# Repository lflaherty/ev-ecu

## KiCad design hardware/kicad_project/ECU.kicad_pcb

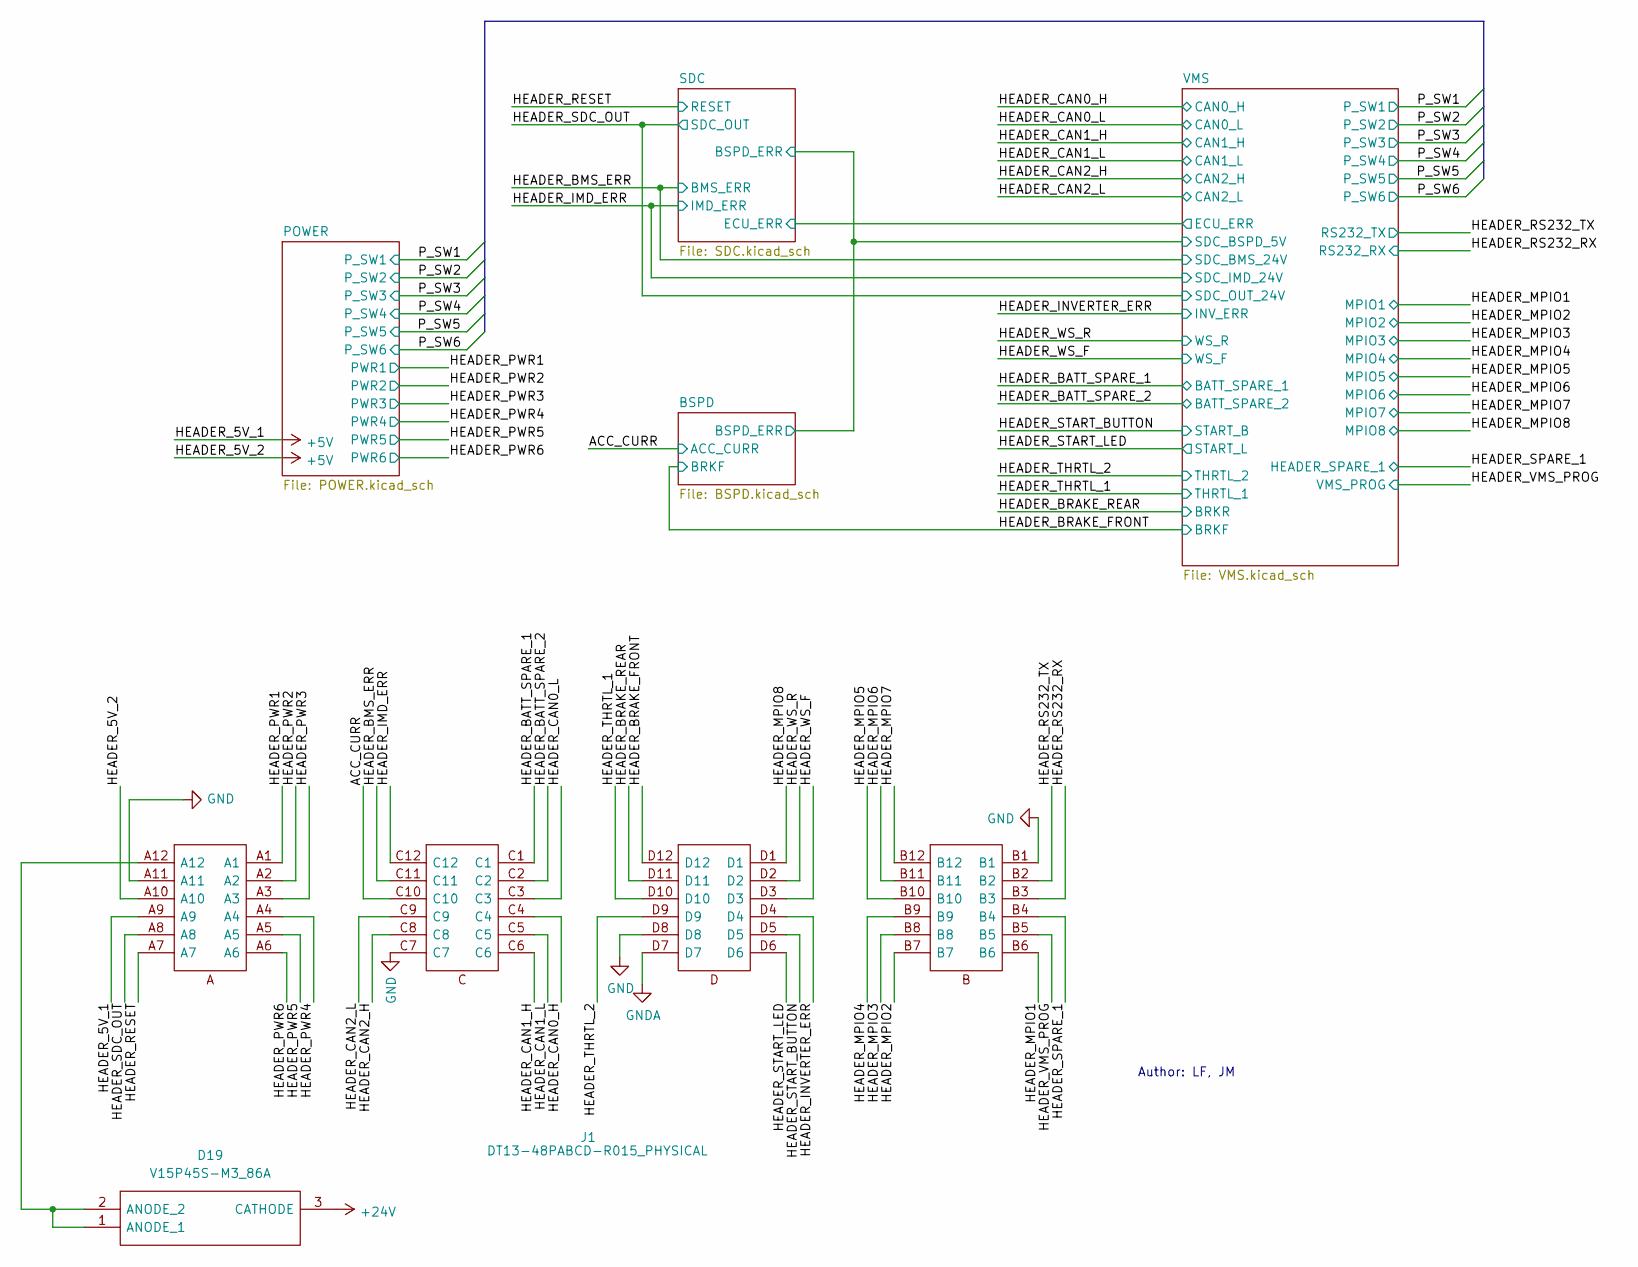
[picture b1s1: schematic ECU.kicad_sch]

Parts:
D19: V15P45S-M3_86A; V15P45SM387A; Manufacturer_Part_Number V15P45S-M3/87A; Mouser Part Number 78-V15P45S-M387A
J1: DT13-48PABCD-R015_PHYSICAL; DT1348PABCDR015_PHYSICAL; Manufacturer_Part_Number DT13-48PABCD-R015; Mouser Part Number 571-DT13-48PABCDR015

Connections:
+5V: J1.A9, J1.A10; also elsewhere on the board
+24V: D19.3 (CATHODE); also elsewhere on the board
/BSPD/ACC_CURR: J1.C10; also elsewhere on the board
/BSPD/BRKF: J1.D12; also elsewhere on the board
/POWER/PWR1: J1.A1; also elsewhere on the board
/POWER/PWR2: J1.A2; also elsewhere on the board
/POWER/PWR3: J1.A3; also elsewhere on the board
/POWER/PWR4: J1.A4; also elsewhere on the board
/POWER/PWR5: J1.A5; also elsewhere on the board
/POWER/PWR6: J1.A6; also elsewhere on the board
/SDC/BMS_ERR: J1.C11; also elsewhere on the board
/SDC/IMD_ERR: J1.C12; also elsewhere on the board
/SDC/RESET: J1.A7; also elsewhere on the board
/SDC/SDC_OUT: J1.A8; also elsewhere on the board
/VMS/BATT_SPARE_1: J1.C1; also elsewhere on the board
/VMS/BATT_SPARE_2: J1.C2; also elsewhere on the board
/VMS/BRKR: J1.D11; also elsewhere on the board
/VMS/CAN0_H: J1.C3; also elsewhere on the board
/VMS/CAN0_L: J1.C4; also elsewhere on the board
/VMS/CAN1_H: J1.C5; also elsewhere on the board
/VMS/CAN1_L: J1.C6; also elsewhere on the board
/VMS/CAN2_H: J1.C9; also elsewhere on the board
/VMS/CAN2_L: J1.C8; also elsewhere on the board
/VMS/HEADER_SPARE_1: J1.B4; also elsewhere on the board
/VMS/INV_ERR: J1.D4; also elsewhere on the board
/VMS/MPIO/MPIO1: J1.B6; also elsewhere on the board
/VMS/MPIO/MPIO2: J1.B7; also elsewhere on the board
/VMS/MPIO/MPIO3: J1.B8; also elsewhere on the board
/VMS/MPIO/MPIO4: J1.B9; also elsewhere on the board
/VMS/MPIO/MPIO5: J1.B10; also elsewhere on the board
/VMS/MPIO/MPIO6: J1.B11; also elsewhere on the board
/VMS/MPIO/MPIO7: J1.B12; also elsewhere on the board
/VMS/MPIO/MPIO8: J1.D1; also elsewhere on the board
/VMS/RS232_RX: J1.B3; also elsewhere on the board
/VMS/RS232_TX: J1.B2; also elsewhere on the board
/VMS/START_B: J1.D5; also elsewhere on the board
/VMS/START_L: J1.D6; also elsewhere on the board
/VMS/THRTL_1: J1.D10; also elsewhere on the board
/VMS/THRTL_2: J1.D9; also elsewhere on the board
/VMS/VMS_PROG: J1.B5; also elsewhere on the board
/VMS/WS_F: J1.D3; also elsewhere on the board
/VMS/WS_R: J1.D2; also elsewhere on the board
GND: J1.A11, J1.B1, J1.C7, J1.D8; also elsewhere on the board
GNDA: J1.D7
unnamed: D19.1 (ANODE_1), D19.2 (ANODE_2), J1.A12

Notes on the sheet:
Author: LF, JM

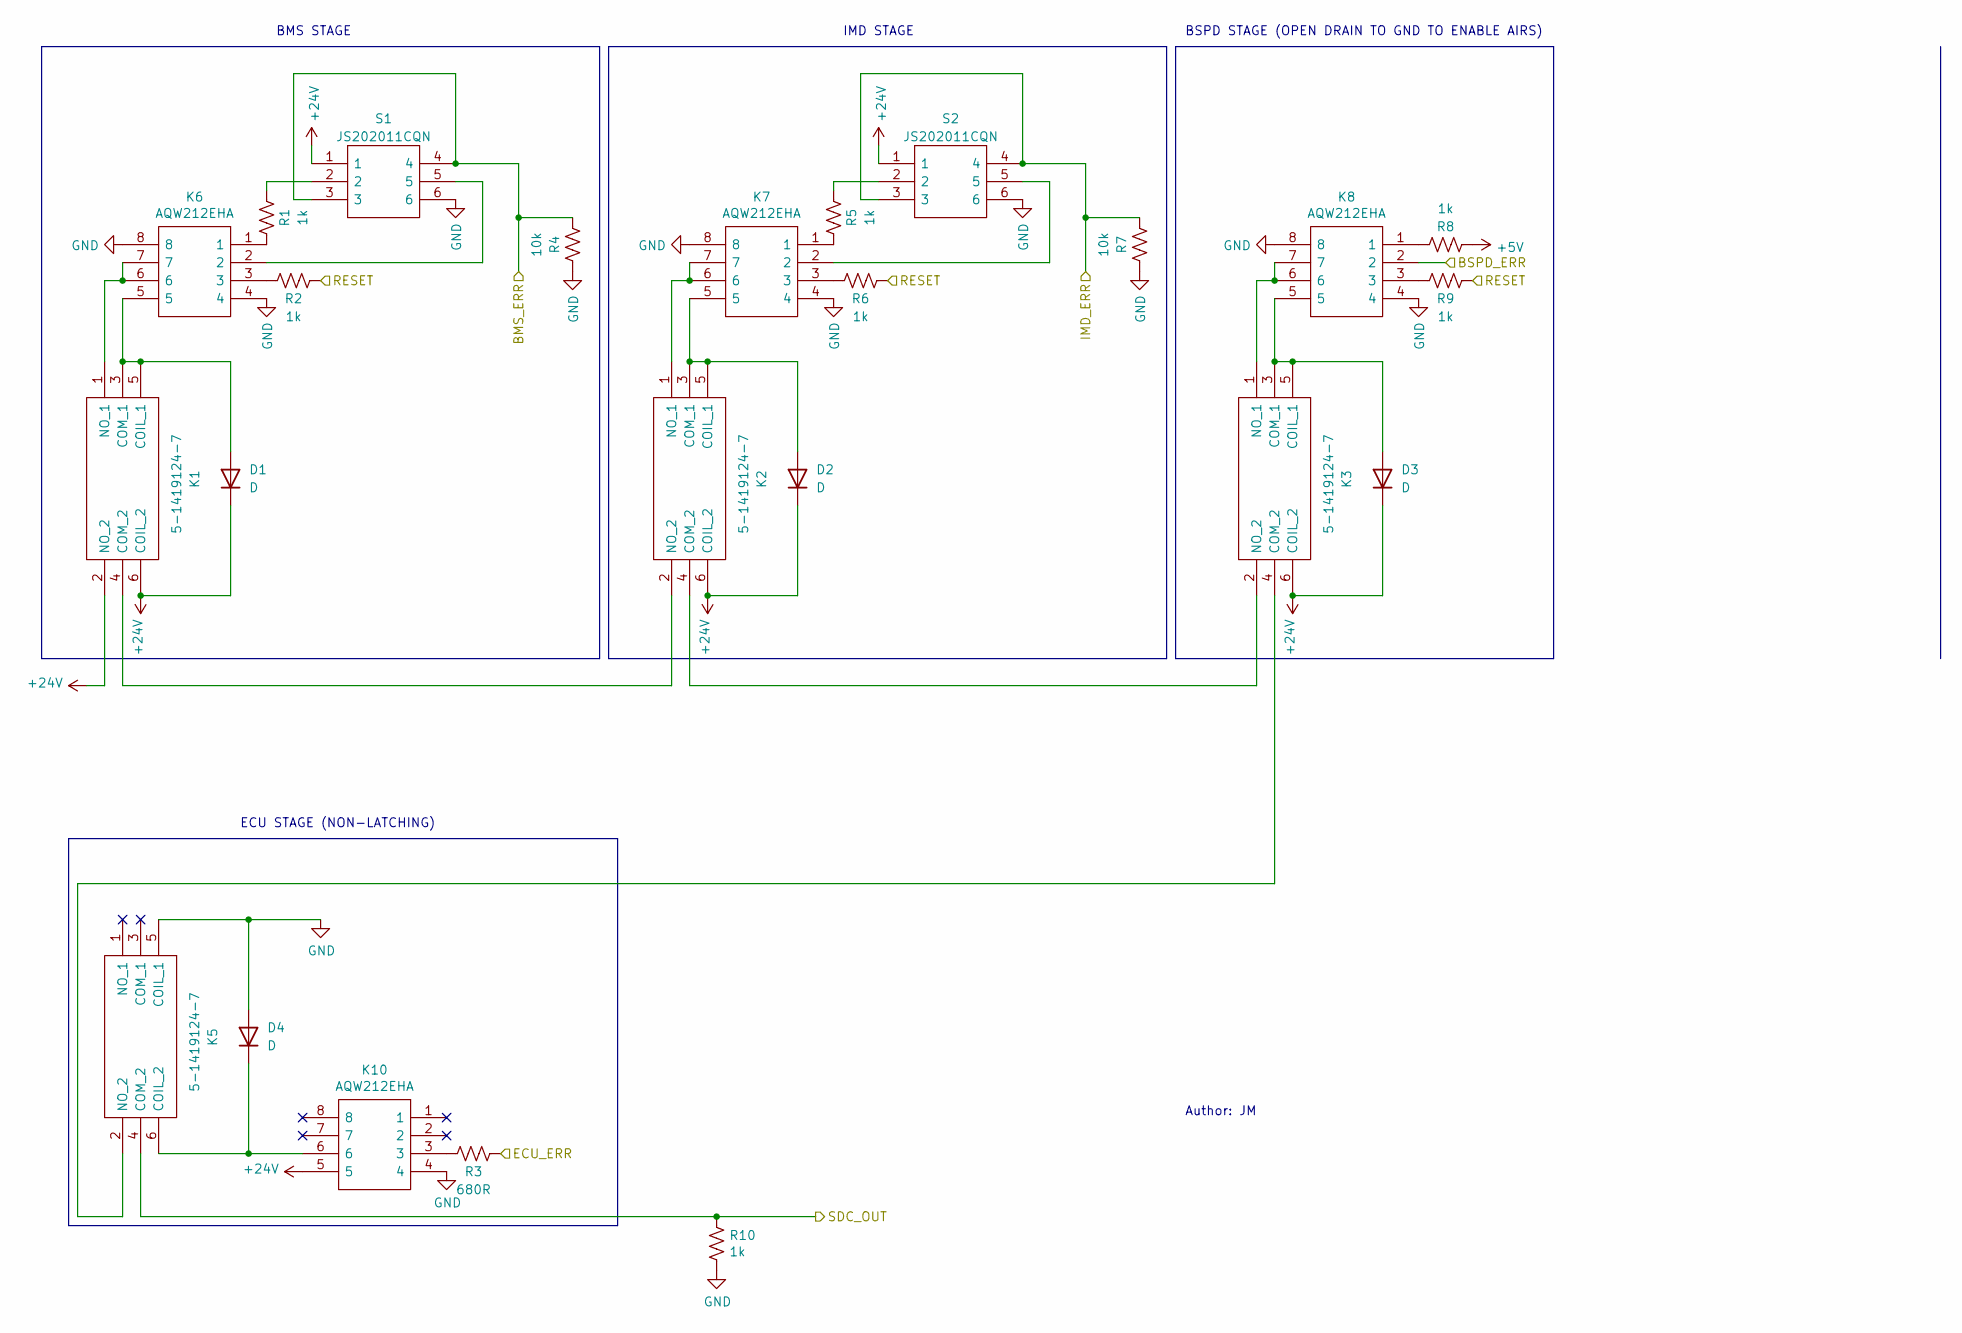
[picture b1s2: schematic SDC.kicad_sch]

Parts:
D1, D2, D3, D4: D; D_SMA
K1, K2, K3, K5: 5-1419124-7; 514191247; Manufacturer_Part_Number 5-1419124-7; Mouser Part Number 655-5-1419124-7
K6, K7, K8, K10: AQW212EHA; SOP254P962X275-8N; Manufacturer_Part_Number AQW212EHA; Mouser Part Number 769-AQW212EHA
R1, R2, R5, R6, R8, R9, R10: 1k; R_0805_2012Metric
R3: 680R; R_0805_2012Metric
R4, R7: 10k; R_0805_2012Metric
S1, S2: JS202011CQN; Manufacturer_Part_Number JS202011CQN; Mouser Part Number 611-JS202011CQN

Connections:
+5V: R8.2; also elsewhere on the board
+24V: D1.1 (K), D2.1 (K), D3.1 (K), K1.2 (NO_2), K1.6 (COIL_2), K2.6 (COIL_2), K3.6 (COIL_2), K10.5, S1.1, S2.1; also elsewhere on the board
/BSPD/BSPD_ERR: K8.2; also elsewhere on the board
/SDC/BMS_ERR: R4.2, S1.3, S1.4; also elsewhere on the board
/SDC/ECU_ERR: R3.1; also elsewhere on the board
/SDC/IMD_ERR: R7.2, S2.3, S2.4; also elsewhere on the board
/SDC/RESET: R2.1, R6.1, R9.1; also elsewhere on the board
/SDC/SDC_OUT: K5.4 (COM_2), R10.1; also elsewhere on the board
GND: D4.2 (A), K5.5 (COIL_1), K6.4, K6.8, K7.4, K7.8, K8.4, K8.8, K10.4, R4.1, R7.1, R10.2, S1.6, S2.6; also elsewhere on the board
unnamed: D1.2 (A), K1.3 (COM_1), K1.5 (COIL_1), K6.5
unnamed: D2.2 (A), K2.3 (COM_1), K2.5 (COIL_1), K7.5
unnamed: D3.2 (A), K3.3 (COM_1), K3.5 (COIL_1), K8.5
unnamed: D4.1 (K), K5.6 (COIL_2), K10.6
unnamed: K1.1 (NO_1), K6.6, K6.7
unnamed: K1.4 (COM_2), K2.2 (NO_2)
unnamed: K2.1 (NO_1), K7.6, K7.7
unnamed: K2.4 (COM_2), K3.2 (NO_2)
unnamed: K3.1 (NO_1), K8.6, K8.7
unnamed: K3.4 (COM_2), K5.2 (NO_2)
unnamed: K6.1, R1.2
unnamed: K6.2, S1.5
unnamed: K6.3, R2.2
unnamed: K7.1, R5.2
unnamed: K7.2, S2.5
unnamed: K7.3, R6.2
unnamed: K8.1, R8.1
unnamed: K8.3, R9.2
unnamed: K10.3, R3.2
unnamed: R1.1, S1.2
unnamed: R5.1, S2.2

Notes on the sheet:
ECU STAGE (NON-LATCHING)
BMS STAGE
Author: JM
BSPD STAGE (OPEN DRAIN TO GND TO ENABLE AIRS)
IMD STAGE

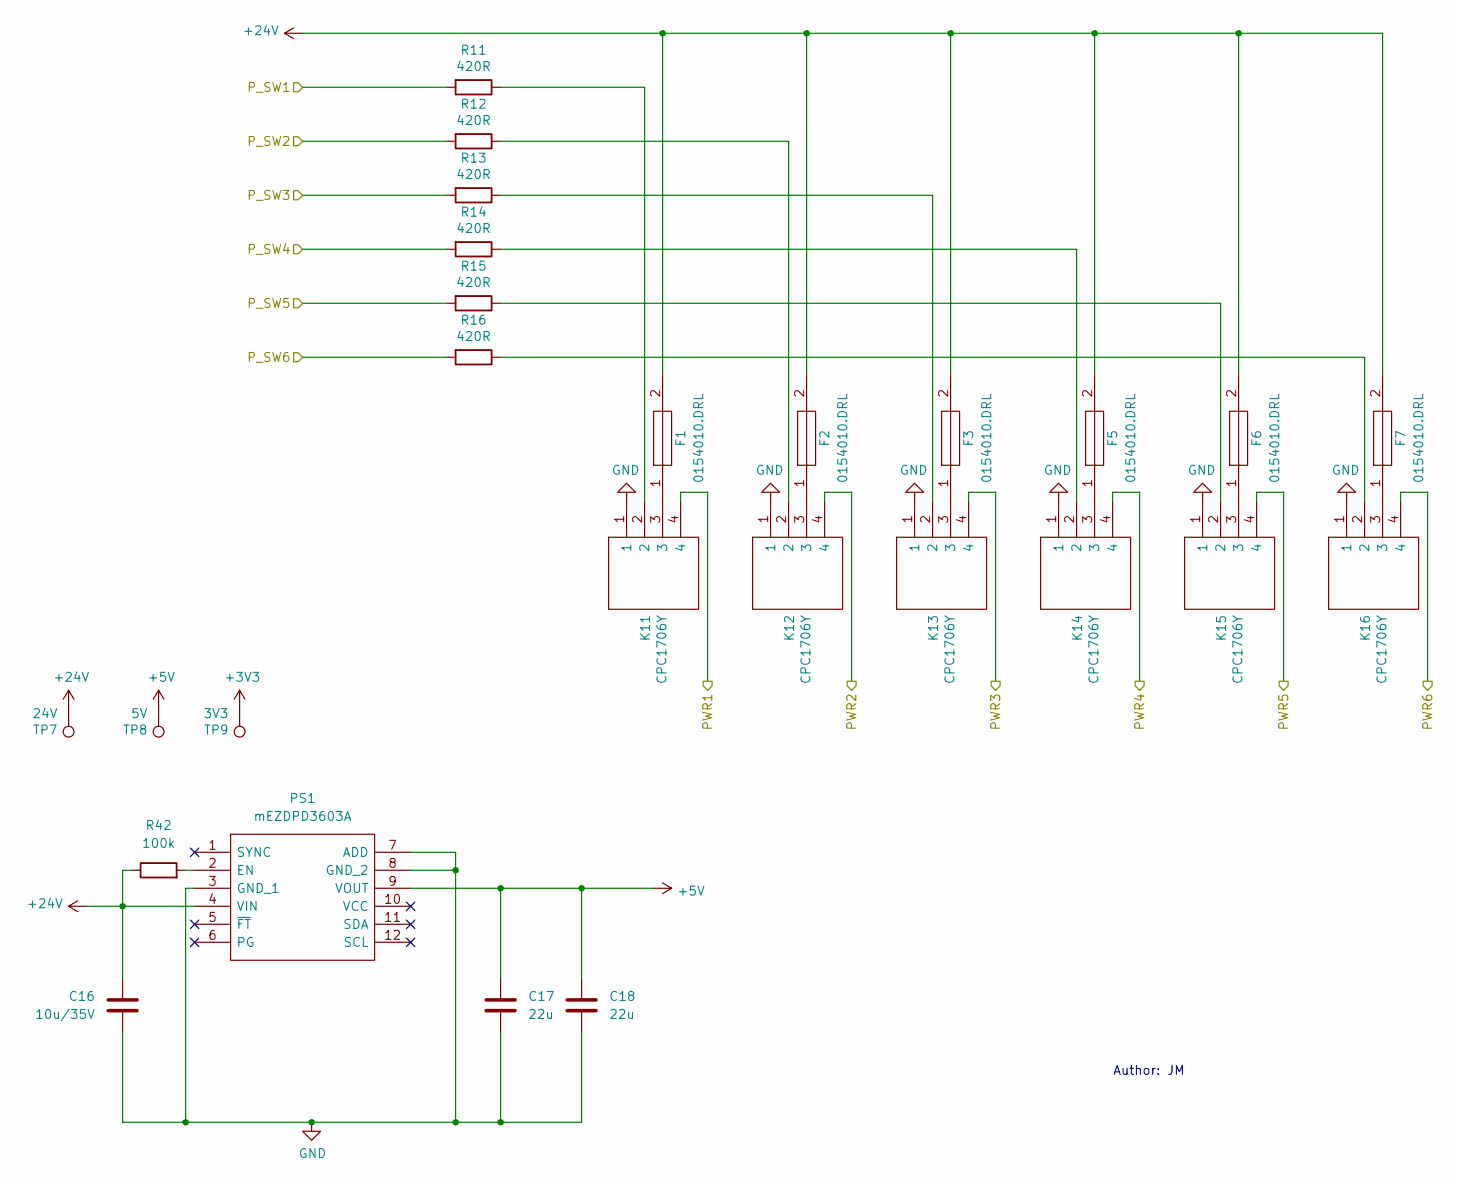
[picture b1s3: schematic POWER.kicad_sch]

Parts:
C16: 10u/35V; C_0805_2012Metric
C17, C18: 22u; C_1206_3216Metric
F1, F2, F3, F5, F6, F7: 0154010.DRL; 0154010DRL; Manufacturer_Part_Number 0154010.DRL; Mouser Part Number 576-0154010.DRL
K11, K12, K13, K14, K15, K16: CPC1706Y; Manufacturer_Part_Number CPC1706Y; Mouser Part Number 849-CPC1706Y
PS1: mEZDPD3603A; Manufacturer_Part_Number mEZDPD3603A; Mouser Part Number 946-MEZDPD3603A
R11, R12, R13, R14, R15, R16: 420R; R_0805_2012Metric
R42: 100k; R_0805_2012Metric
TP7: 24V; TestPoint_THTPad_D2.5mm_Drill1.2mm
TP8: 5V; TestPoint_THTPad_D2.5mm_Drill1.2mm
TP9: 3V3; TestPoint_THTPad_D2.5mm_Drill1.2mm

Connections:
+5V: C17.1, C18.1, PS1.9 (VOUT), TP8.1; also elsewhere on the board
+24V: C16.2, F1.2, F2.2, F3.2, F5.2, F6.2, F7.2, PS1.4 (VIN), R42.1, TP7.1; also elsewhere on the board
/POWER/PWR1: K11.4; also elsewhere on the board
/POWER/PWR2: K12.4; also elsewhere on the board
/POWER/PWR3: K13.4; also elsewhere on the board
/POWER/PWR4: K14.4; also elsewhere on the board
/POWER/PWR5: K15.4; also elsewhere on the board
/POWER/PWR6: K16.4; also elsewhere on the board
/POWER/P_SW1: R11.2; also elsewhere on the board
/POWER/P_SW2: R12.2; also elsewhere on the board
/POWER/P_SW3: R13.2; also elsewhere on the board
/POWER/P_SW4: R14.2; also elsewhere on the board
/POWER/P_SW5: R15.2; also elsewhere on the board
/POWER/P_SW6: R16.2; also elsewhere on the board
GND: C16.1, C17.2, C18.2, K11.1, K12.1, K13.1, K14.1, K15.1, K16.1, PS1.3 (GND_1), PS1.7 (ADD), PS1.8 (GND_2); also elsewhere on the board
unnamed: F1.1, K11.3
unnamed: F2.1, K12.3
unnamed: F3.1, K13.3
unnamed: F5.1, K14.3
unnamed: F6.1, K15.3
unnamed: F7.1, K16.3
unnamed: K11.2, R11.1
unnamed: K12.2, R12.1
unnamed: K13.2, R13.1
unnamed: K14.2, R14.1
unnamed: K15.2, R15.1
unnamed: K16.2, R16.1
unnamed: PS1.2 (EN), R42.2

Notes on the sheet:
Author: JM

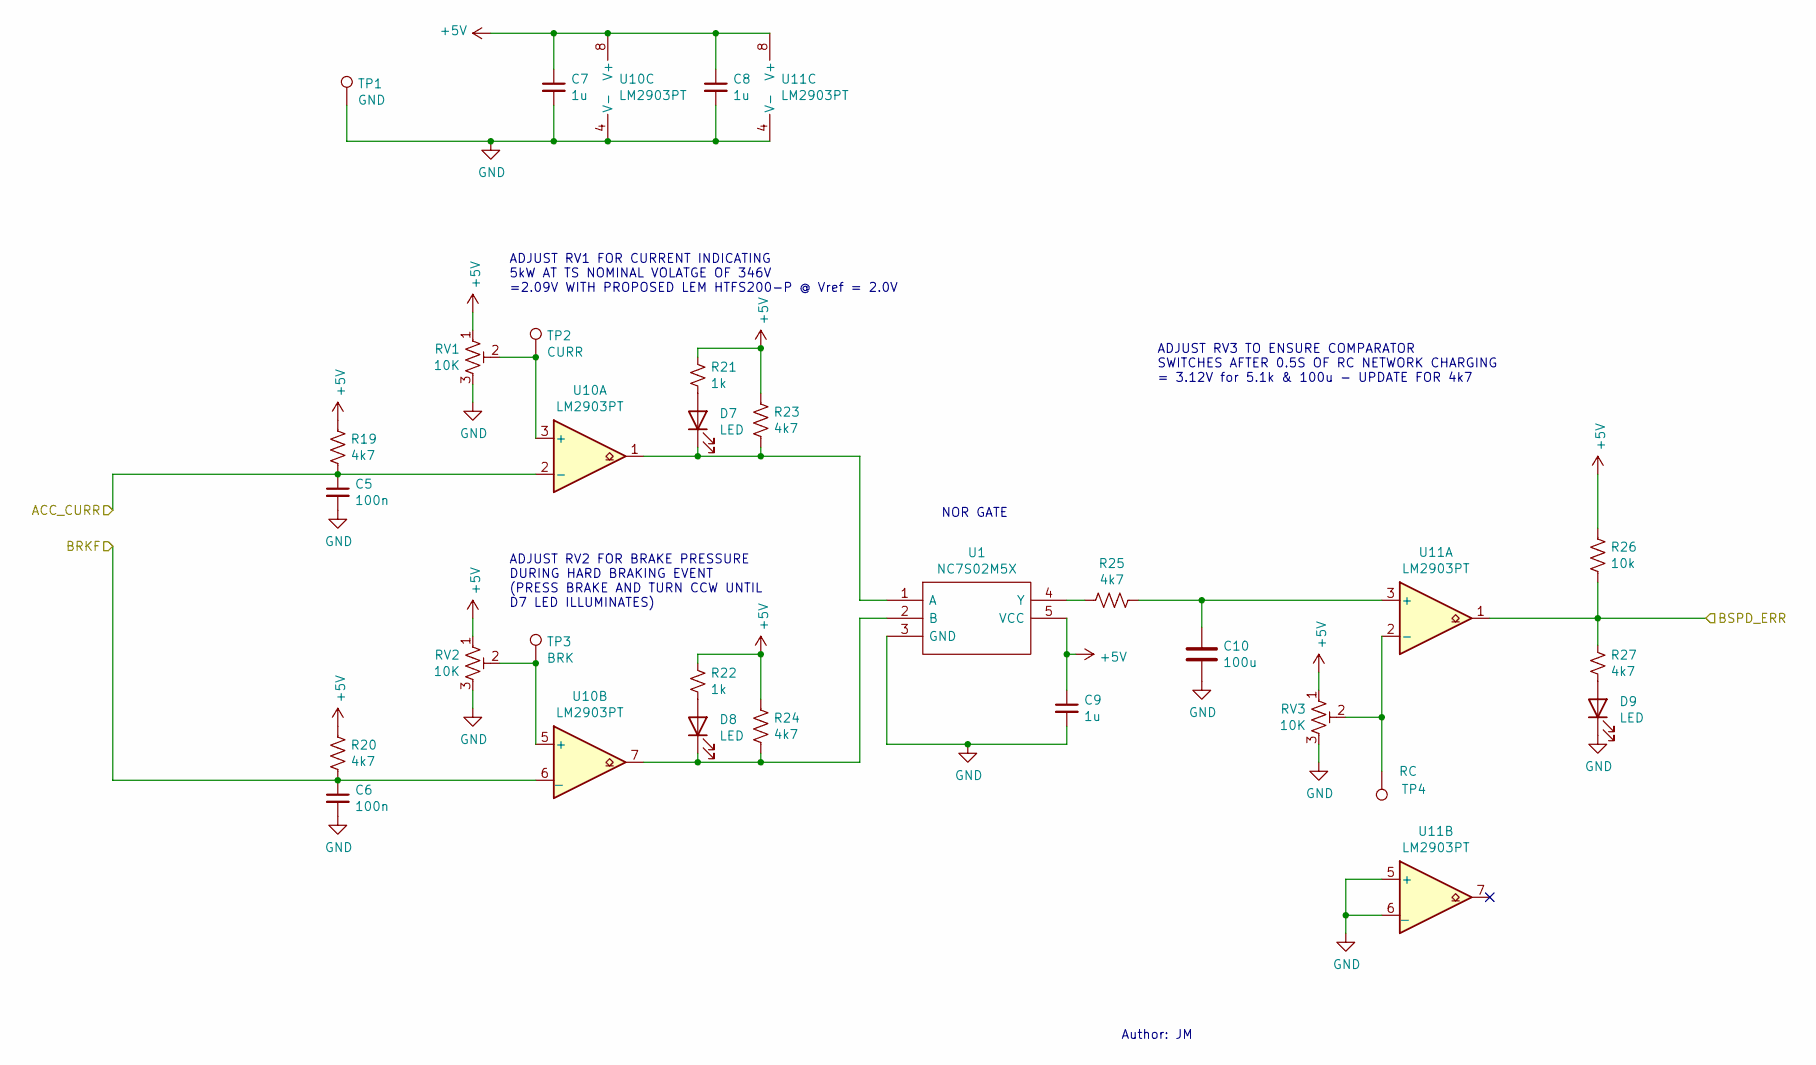
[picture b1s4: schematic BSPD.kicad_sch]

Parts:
C5, C6: 100n; C_0805_2012Metric
C7, C8, C9: 1u; C_0805_2012Metric
C10: 100u; C_1206_3216Metric
D7, D8, D9: LED; LED_0805_2012Metric
R19, R20, R23, R24, R25, R27: 4k7; R_0805_2012Metric
R21, R22: 1k; R_0805_2012Metric
R26: 10k; R_0805_2012Metric
RV1, RV2, RV3: 10K; 3306F1103
TP1: GND; TestPoint_THTPad_D2.5mm_Drill1.2mm
TP2: CURR; TestPoint_THTPad_D2.5mm_Drill1.2mm
TP3: BRK; TestPoint_THTPad_D2.5mm_Drill1.2mm
TP4: RC; TestPoint_THTPad_D2.5mm_Drill1.2mm
U1: NC7S02M5X; SOT95P280X125-5N; Manufacturer_Part_Number NC7S02M5X; Mouser Part Number 512-NC7S02M5X
U10, U11: LM2903PT; TSSOP-8_4.4x3mm_P0.65mm

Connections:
+5V: C7.1, C8.1, C9.1, R19.1, R20.1, R21.1, R22.1, R23.1, R24.1, R26.1, RV1.1, RV2.1, RV3.1, U1.5 (VCC), U10.8 (V+), U11.8 (V+); also elsewhere on the board
/BSPD/ACC_CURR: C5.1, R19.2, U10.2 (-); also elsewhere on the board
/BSPD/BRKF: C6.1, R20.2, U10.6 (_); also elsewhere on the board
/BSPD/BSPD_ERR: R26.2, R27.1, U11.1; also elsewhere on the board
GND: C5.2, C6.2, C7.2, C8.2, C9.2, C10.2, D9.1 (K), RV1.3, RV2.3, RV3.3, TP1.1, U1.3 (GND), U10.4 (V-), U11.4 (V-), U11.5 (+), U11.6 (_); also elsewhere on the board
unnamed: C10.1, R25.1, U11.3 (+)
unnamed: D7.1 (K), R23.2, U1.1 (A), U10.1
unnamed: D7.2 (A), R21.2
unnamed: D8.1 (K), R24.2, U1.2 (B), U10.7
unnamed: D8.2 (A), R22.2
unnamed: D9.2 (A), R27.2
unnamed: R25.2, U1.4 (Y)
unnamed: RV1.2, TP2.1, U10.3 (+)
unnamed: RV2.2, TP3.1, U10.5 (+)
unnamed: RV3.2, TP4.1, U11.2 (-)

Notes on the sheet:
ADJUST RV1 FOR CURRENT INDICATING 5kW AT TS NOMINAL VOLATGE OF 346V =2.09V WITH PROPOSED LEM HTFS200-P @ Vref = 2.0V
NOR GATE
ADJUST RV3 TO ENSURE COMPARATOR SWITCHES AFTER 0.5S OF RC NETWORK CHARGING = 3.12V for 5.1k & 100u - UPDATE FOR 4k7
Author: JM
ADJUST RV2 FOR BRAKE PRESSURE DURING HARD BRAKING EVENT (PRESS BRAKE AND TURN CCW UNTIL D7 LED ILLUMINATES)

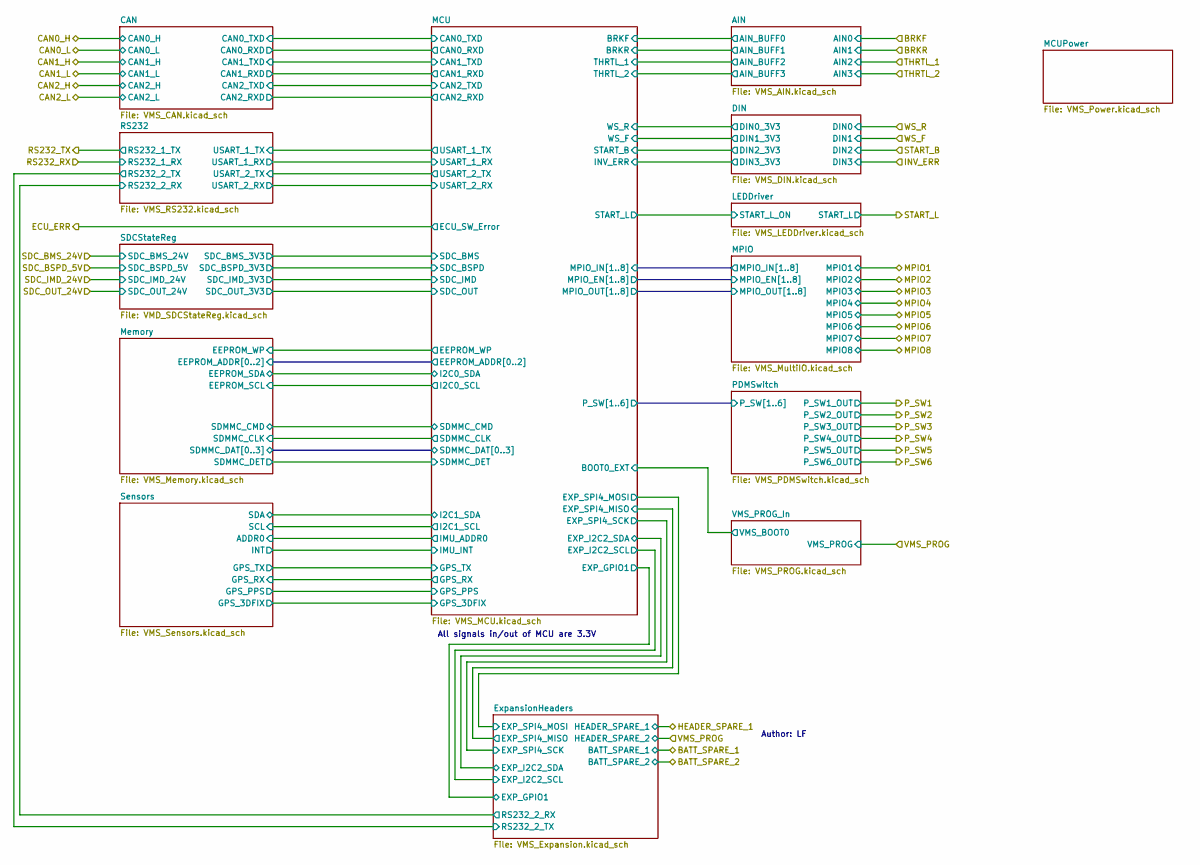
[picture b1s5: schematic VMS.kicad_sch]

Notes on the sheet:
All signals in/out of MCU are 3.3V
Author: LF

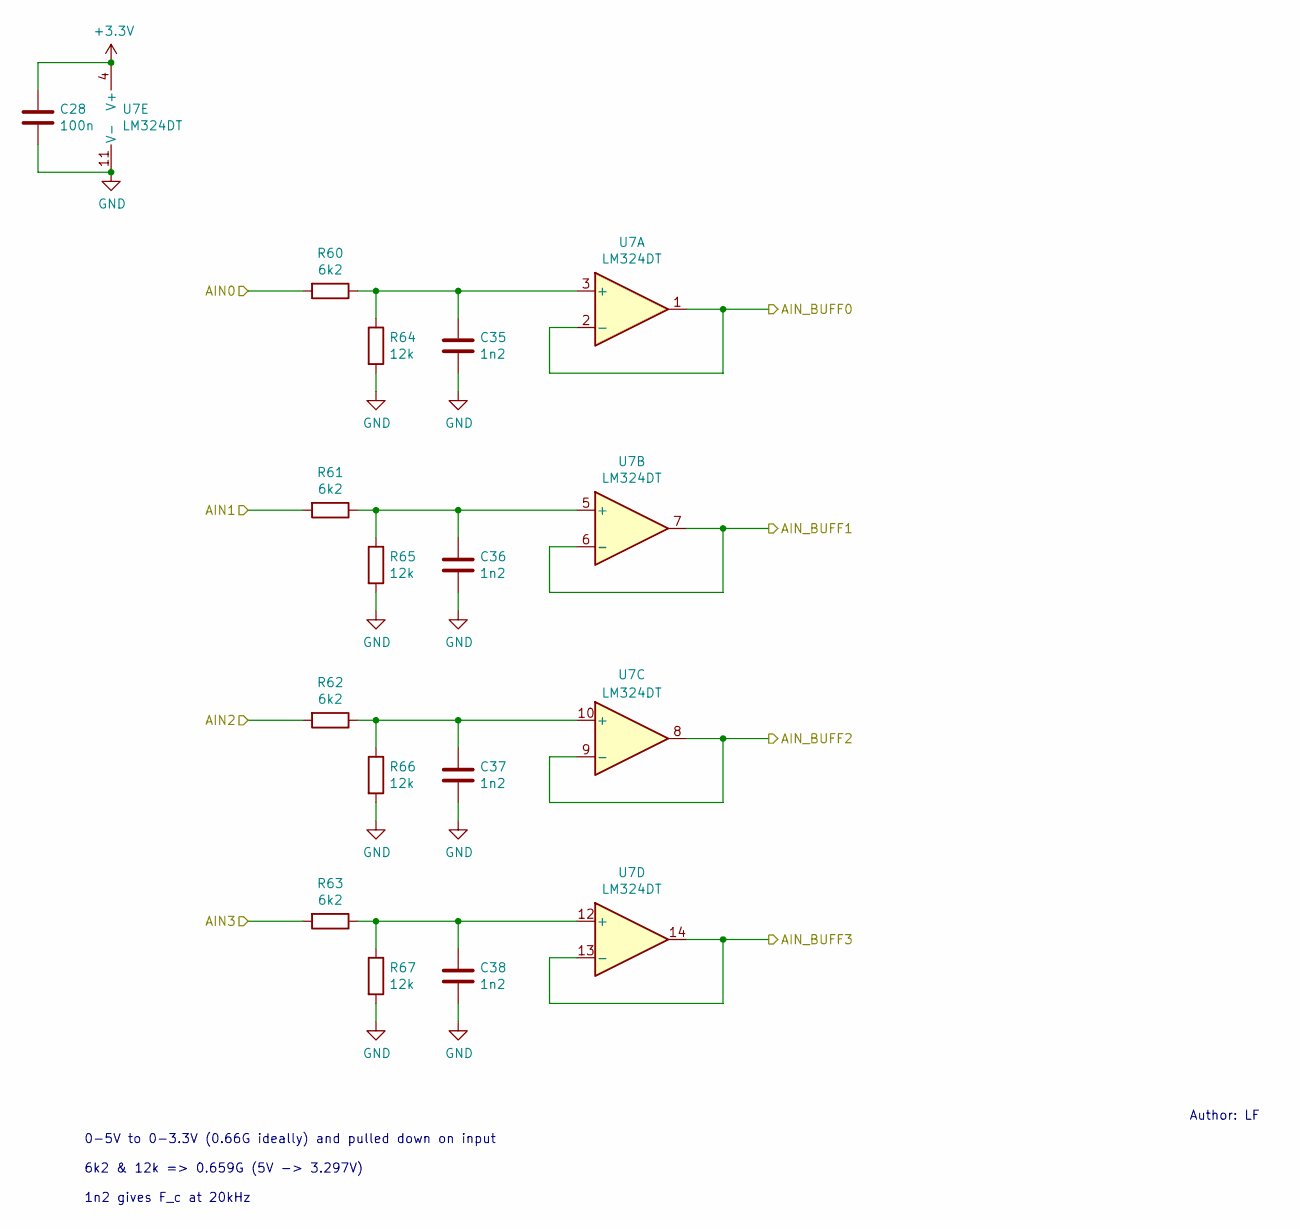
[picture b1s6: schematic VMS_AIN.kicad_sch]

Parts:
C28: 100n; C_0805_2012Metric
C35, C36, C37, C38: 1n2; C_0805_2012Metric
R60, R61, R62, R63: 6k2; R_0805_2012Metric
R64, R65, R66, R67: 12k; R_0805_2012Metric
U7: LM324DT; SOIC-14_3.9x8.7mm_P1.27mm

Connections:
/BSPD/BRKF: R60.2; also elsewhere on the board
/VMS/AIN/AIN_BUFF0: U7.1, U7.2 (-); also elsewhere on the board
/VMS/AIN/AIN_BUFF1: U7.6 (-), U7.7; also elsewhere on the board
/VMS/AIN/AIN_BUFF2: U7.8, U7.9 (-); also elsewhere on the board
/VMS/AIN/AIN_BUFF3: U7.13 (-), U7.14; also elsewhere on the board
/VMS/BRKR: R61.2; also elsewhere on the board
/VMS/THRTL_1: R62.2; also elsewhere on the board
/VMS/THRTL_2: R63.2; also elsewhere on the board
GND: C28.2, C35.2, C36.2, C37.2, C38.2, R64.2, R65.2, R66.2, R67.2, U7.11 (V-); also elsewhere on the board
unnamed: C35.1, R60.1, R64.1, U7.3 (+)
unnamed: C36.1, R61.1, R65.1, U7.5 (+)
unnamed: C37.1, R62.1, R66.1, U7.10 (+)
unnamed: C38.1, R63.1, R67.1, U7.12 (+)

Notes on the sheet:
0-5V to 0-3.3V (0.66G ideally) and pulled down on input 6k2 & 12k => 0.659G (5V -> 3.297V) 1n2 gives F_c at 20kHz
Author: LF

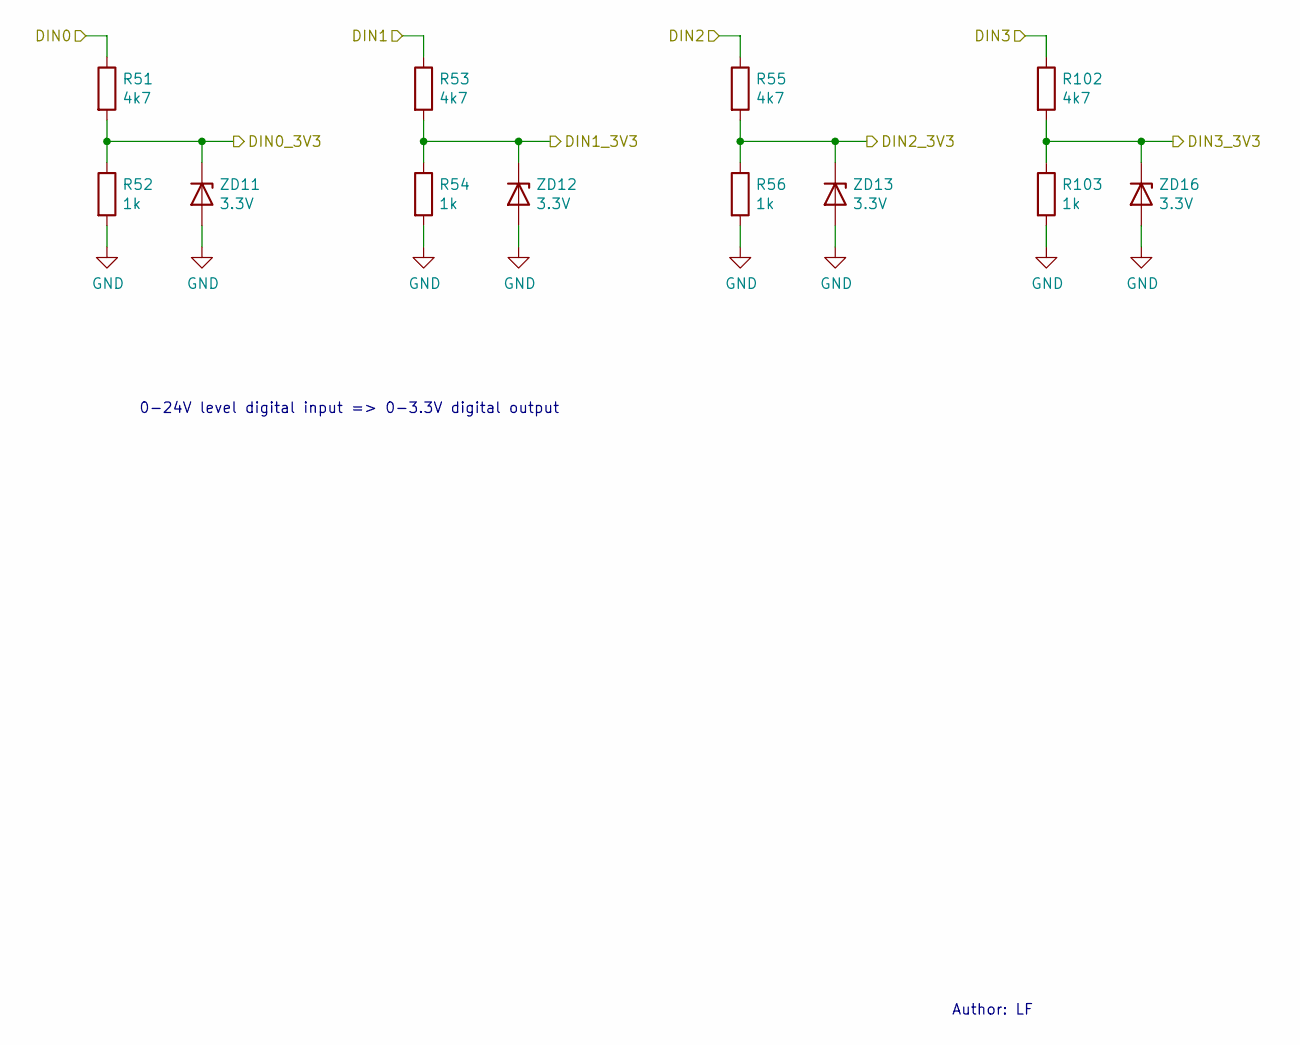
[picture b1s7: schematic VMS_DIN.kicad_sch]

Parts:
R51, R53, R55, R102: 4k7; R_0805_2012Metric
R52, R54, R56, R103: 1k; R_0805_2012Metric
ZD11, ZD12, ZD13, ZD16: 3.3V; D_MiniMELF

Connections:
/VMS/DIN/DIN0_3V3: R51.2, R52.1, ZD11.1 (K); also elsewhere on the board
/VMS/DIN/DIN1_3V3: R53.2, R54.1, ZD12.1 (K); also elsewhere on the board
/VMS/DIN/DIN2_3V3: R55.2, R56.1, ZD13.1 (K); also elsewhere on the board
/VMS/DIN/DIN3_3V3: R102.2, R103.1, ZD16.1 (K); also elsewhere on the board
/VMS/INV_ERR: R102.1; also elsewhere on the board
/VMS/START_B: R55.1; also elsewhere on the board
/VMS/WS_F: R53.1; also elsewhere on the board
/VMS/WS_R: R51.1; also elsewhere on the board
GND: R52.2, R54.2, R56.2, R103.2, ZD11.2 (A), ZD12.2 (A), ZD13.2 (A), ZD16.2 (A); also elsewhere on the board

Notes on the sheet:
Author: LF
0-24V level digital input => 0-3.3V digital output

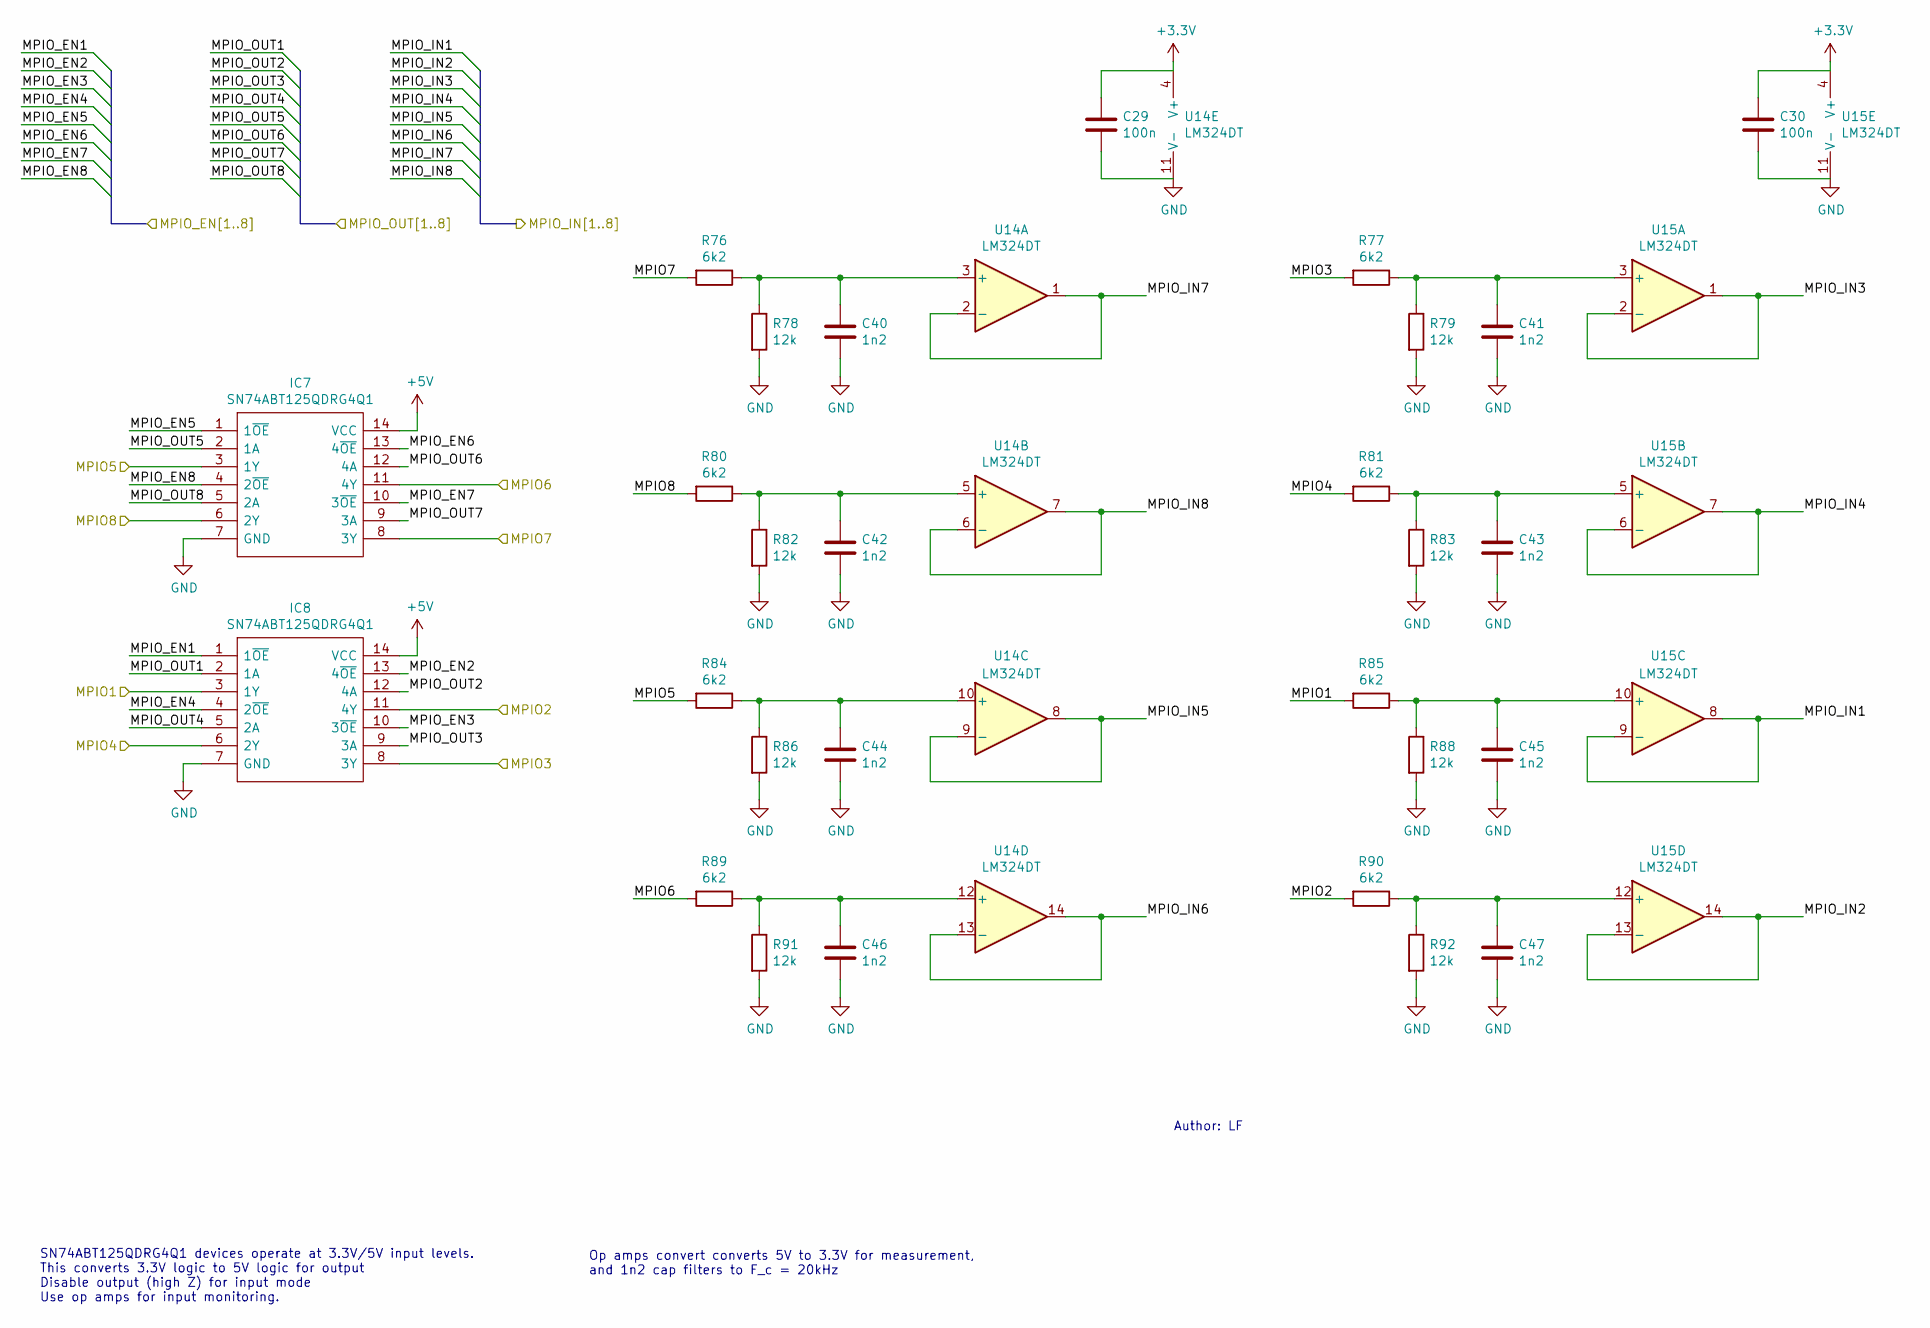
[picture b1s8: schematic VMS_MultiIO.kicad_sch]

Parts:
C29, C30: 100n; C_0805_2012Metric
C40, C41, C42, C43, C44, C45, C46, C47: 1n2; C_0805_2012Metric
IC7, IC8: SN74ABT125QDRG4Q1; SOIC-14_3.9x8.7mm_P1.27mm; Manufacturer_Part_Number SN74ABT125QDRG4Q1; Mouser Part Number 595-N74ABT125QDRG4Q1
R76, R77, R80, R81, R84, R85, R89, R90: 6k2; R_0805_2012Metric
R78, R79, R82, R83, R86, R88, R91, R92: 12k; R_0805_2012Metric
U14, U15: LM324DT; SOIC-14_3.9x8.7mm_P1.27mm

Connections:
+5V: IC7.14 (VCC), IC8.14 (VCC); also elsewhere on the board
/VMS/MCU/MPIO_EN1: IC8.1 (1~OE); also elsewhere on the board
/VMS/MCU/MPIO_EN2: IC8.13 (4~OE); also elsewhere on the board
/VMS/MCU/MPIO_EN3: IC8.10 (3~OE); also elsewhere on the board
/VMS/MCU/MPIO_EN4: IC8.4 (2~OE); also elsewhere on the board
/VMS/MCU/MPIO_EN5: IC7.1 (1~OE); also elsewhere on the board
/VMS/MCU/MPIO_EN6: IC7.13 (4~OE); also elsewhere on the board
/VMS/MCU/MPIO_EN7: IC7.10 (3~OE); also elsewhere on the board
/VMS/MCU/MPIO_EN8: IC7.4 (2~OE); also elsewhere on the board
/VMS/MCU/MPIO_IN1: U15.8, U15.9 (-); also elsewhere on the board
/VMS/MCU/MPIO_IN2: U15.13 (-), U15.14; also elsewhere on the board
/VMS/MCU/MPIO_IN3: U15.1, U15.2 (-); also elsewhere on the board
/VMS/MCU/MPIO_IN4: U15.6 (-), U15.7; also elsewhere on the board
/VMS/MCU/MPIO_IN5: U14.8, U14.9 (-); also elsewhere on the board
/VMS/MCU/MPIO_IN6: U14.13 (-), U14.14; also elsewhere on the board
/VMS/MCU/MPIO_IN7: U14.1, U14.2 (-); also elsewhere on the board
/VMS/MCU/MPIO_IN8: U14.6 (-), U14.7; also elsewhere on the board
/VMS/MCU/MPIO_OUT1: IC8.2 (1A); also elsewhere on the board
/VMS/MCU/MPIO_OUT2: IC8.12 (4A); also elsewhere on the board
/VMS/MCU/MPIO_OUT3: IC8.9 (3A); also elsewhere on the board
/VMS/MCU/MPIO_OUT4: IC8.5 (2A); also elsewhere on the board
/VMS/MCU/MPIO_OUT5: IC7.2 (1A); also elsewhere on the board
/VMS/MCU/MPIO_OUT6: IC7.12 (4A); also elsewhere on the board
/VMS/MCU/MPIO_OUT7: IC7.9 (3A); also elsewhere on the board
/VMS/MCU/MPIO_OUT8: IC7.5 (2A); also elsewhere on the board
/VMS/MPIO/MPIO1: IC8.3 (1Y), R85.2; also elsewhere on the board
/VMS/MPIO/MPIO2: IC8.11 (4Y), R90.2; also elsewhere on the board
/VMS/MPIO/MPIO3: IC8.8 (3Y), R77.2; also elsewhere on the board
/VMS/MPIO/MPIO4: IC8.6 (2Y), R81.2; also elsewhere on the board
/VMS/MPIO/MPIO5: IC7.3 (1Y), R84.2; also elsewhere on the board
/VMS/MPIO/MPIO6: IC7.11 (4Y), R89.2; also elsewhere on the board
/VMS/MPIO/MPIO7: IC7.8 (3Y), R76.2; also elsewhere on the board
/VMS/MPIO/MPIO8: IC7.6 (2Y), R80.2; also elsewhere on the board
GND: C29.2, C30.2, C40.2, C41.2, C42.2, C43.2, C44.2, C45.2, C46.2, C47.2, IC7.7 (GND), IC8.7 (GND), R78.2, R79.2, R82.2, R83.2, R86.2, R88.2, R91.2, R92.2, U14.11 (V-), U15.11 (V-); also elsewhere on the board
unnamed: C40.1, R76.1, R78.1, U14.3 (+)
unnamed: C41.1, R77.1, R79.1, U15.3 (+)
unnamed: C42.1, R80.1, R82.1, U14.5 (+)
unnamed: C43.1, R81.1, R83.1, U15.5 (+)
unnamed: C44.1, R84.1, R86.1, U14.10 (+)
unnamed: C45.1, R85.1, R88.1, U15.10 (+)
unnamed: C46.1, R89.1, R91.1, U14.12 (+)
unnamed: C47.1, R90.1, R92.1, U15.12 (+)

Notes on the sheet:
SN74ABT125QDRG4Q1 devices operate at 3.3V/5V input levels. This converts 3.3V logic to 5V logic for output Disable output (high Z) for input mode Use op amps for input monitoring.
Author: LF
Op amps convert converts 5V to 3.3V for measurement, and 1n2 cap filters to F_c = 20kHz
